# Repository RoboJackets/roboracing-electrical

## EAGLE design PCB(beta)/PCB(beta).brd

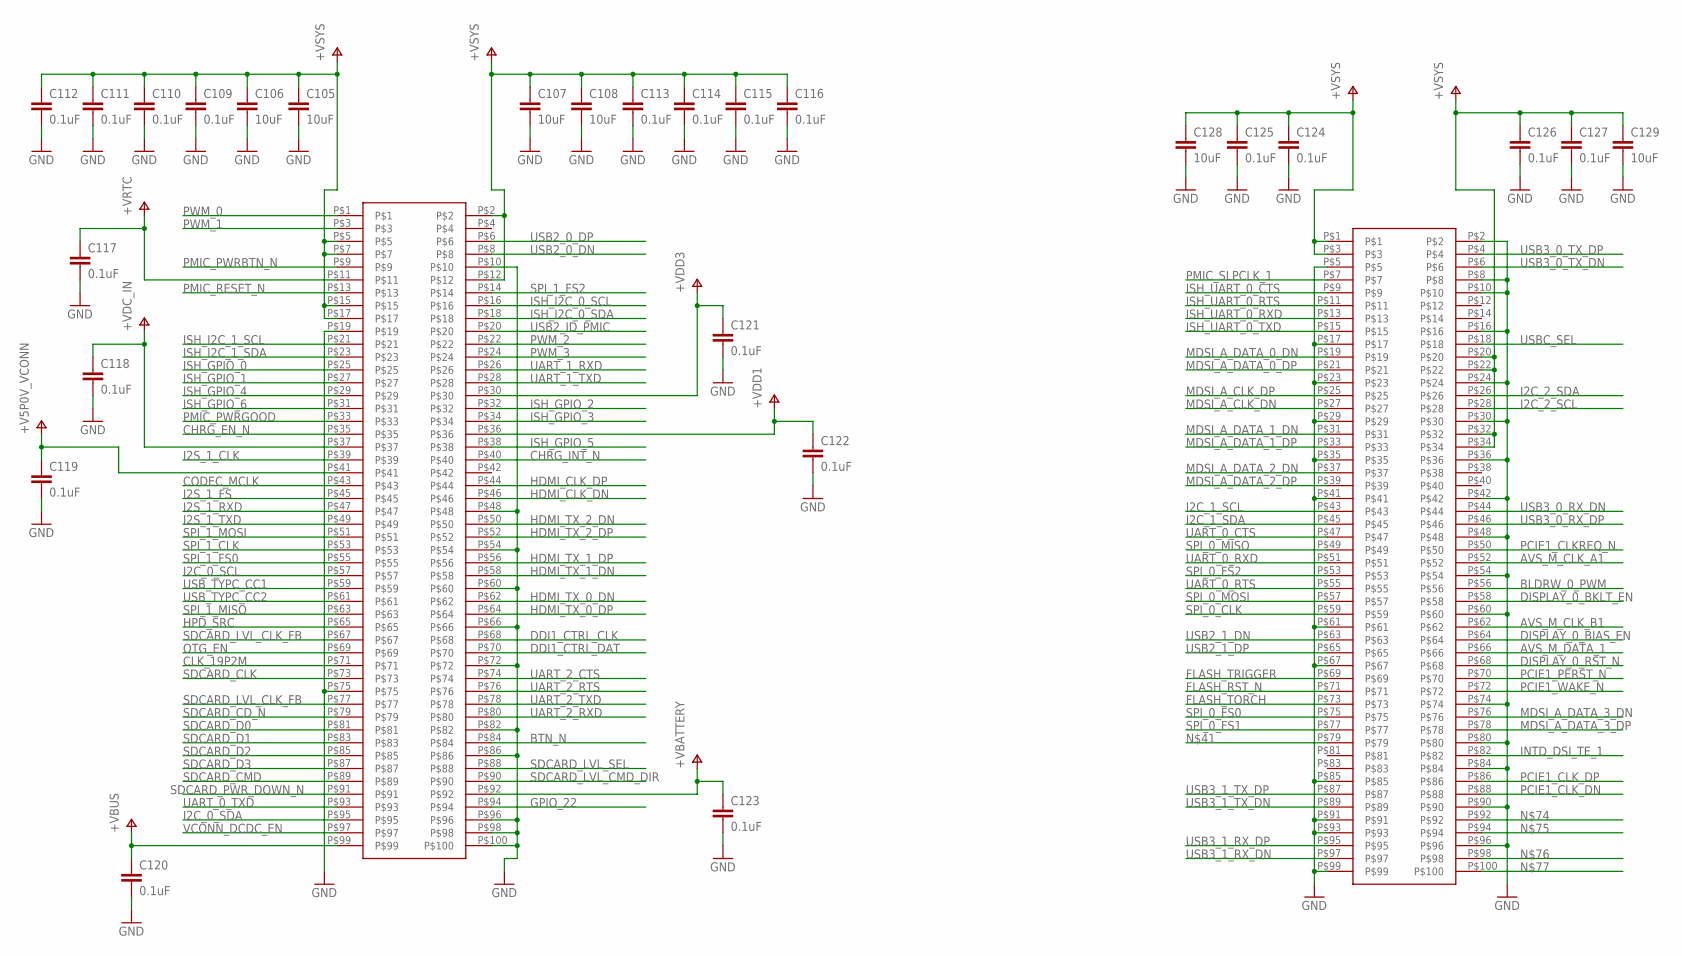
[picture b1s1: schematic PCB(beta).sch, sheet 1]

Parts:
C105, C106, C107, C108, C128, C129: 10uF; 0603
C109, C110, C111, C112, C113, C114, C115, C116, C117, C118, C119, C120, C121, C122, C123, C124, C125, C126, C127: 0.1uF; 0603
U$55, U$56: DF40C-100DS-0.4V(51)_100PINCONNECTOR; 100-DF40

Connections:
+V5P0V_VCONN: C119.1, U$55.P$41
+VBATTERY: C123.1, U$55.P$92; also elsewhere on the board
+VBUS: C120.1, U$55.P$99; also elsewhere on the board
+VDC_IN: C118.1, U$55.P$37; also elsewhere on the board
+VDD1: C122.1, U$55.P$36; also elsewhere on the board
+VDD3: C121.1, U$55.P$30; also elsewhere on the board
+VRTC: C117.1, U$55.P$11; also elsewhere on the board
+VSYS: C105.1, C106.1, C107.1, C108.1, C109.1, C110.1, C111.1, C112.1, C113.1, C114.1, C115.1, C116.1, U$55.P$2, U$55.P$5, U$55.P$7, U$55.P$12, U$55.P$15, U$55.P$17; also elsewhere on the board
AVS_M_CLK_A1: U$56.P$52; also elsewhere on the board
AVS_M_CLK_B1: U$56.P$62; also elsewhere on the board
AVS_M_DATA_1: U$56.P$66; also elsewhere on the board
BLDRW_0_PWM: U$56.P$56; also elsewhere on the board
BTN_N: U$55.P$84; also elsewhere on the board
CHRG_EN_N: U$55.P$35; also elsewhere on the board
CHRG_INT_N: U$55.P$40; also elsewhere on the board
CLK_19P2M: U$55.P$71; also elsewhere on the board
CODEC_MCLK: U$55.P$43; also elsewhere on the board
DDI1_CTRL_CLK: U$55.P$68; also elsewhere on the board
DDI1_CTRL_DAT: U$55.P$70; also elsewhere on the board
DISPLAY_0_BIAS_EN: U$56.P$64; also elsewhere on the board
DISPLAY_0_BKLT_EN: U$56.P$58; also elsewhere on the board
DISPLAY_0_RST_N: U$56.P$68; also elsewhere on the board
FLASH_RST_N: U$56.P$71; also elsewhere on the board
FLASH_TORCH: U$56.P$73; also elsewhere on the board
FLASH_TRIGGER: U$56.P$69; also elsewhere on the board
GND: C105.2, C106.2, C107.2, C108.2, C109.2, C110.2, C111.2, C112.2, C113.2, C114.2, C115.2, C116.2, C117.2, C118.2, C119.2, C120.2, C121.2, C122.2, C123.2, C124.2, C125.2, C126.2, C127.2, C128.2, C129.2, U$55.P$10, U$55.P$19, U$55.P$48, U$55.P$54, U$55.P$60, U$55.P$66, U$55.P$72, U$55.P$75, U$55.P$82, U$55.P$86, U$55.P$96, U$55.P$98, U$55.P$100, U$56.P$2, U$56.P$5, U$56.P$8, U$56.P$10, U$56.P$16, U$56.P$17, U$56.P$23, U$56.P$24, U$56.P$29, U$56.P$30, U$56.P$35, U$56.P$36, U$56.P$41, U$56.P$42, U$56.P$48, U$56.P$54, U$56.P$60, U$56.P$61, U$56.P$67, U$56.P$74, U$56.P$80, U$56.P$84, U$56.P$85, U$56.P$90, U$56.P$91, U$56.P$93, U$56.P$96, U$56.P$99; also elsewhere on the board
GPIO_22: U$55.P$94; also elsewhere on the board
HDMI_CLK_DN: U$55.P$46; also elsewhere on the board
HDMI_CLK_DP: U$55.P$44; also elsewhere on the board
HDMI_TX_0_DN: U$55.P$62; also elsewhere on the board
HDMI_TX_0_DP: U$55.P$64; also elsewhere on the board
HDMI_TX_1_DN: U$55.P$58; also elsewhere on the board
HDMI_TX_1_DP: U$55.P$56; also elsewhere on the board
HDMI_TX_2_DN: U$55.P$50; also elsewhere on the board
HDMI_TX_2_DP: U$55.P$52; also elsewhere on the board
HPD_SRC: U$55.P$65; also elsewhere on the board
I2C_0_SCL: U$55.P$57; also elsewhere on the board
I2C_0_SDA: U$55.P$95; also elsewhere on the board
I2C_1_SCL: U$56.P$43; also elsewhere on the board
I2C_1_SDA: U$56.P$45; also elsewhere on the board
I2C_2_SCL: U$56.P$28; also elsewhere on the board
I2C_2_SDA: U$56.P$26; also elsewhere on the board
I2S_1_CLK: U$55.P$39; also elsewhere on the board
I2S_1_FS: U$55.P$45; also elsewhere on the board
I2S_1_RXD: U$55.P$47; also elsewhere on the board
I2S_1_TXD: U$55.P$49; also elsewhere on the board
INTD_DSI_TE_1: U$56.P$82
ISH_GPIO_0: U$55.P$25; also elsewhere on the board
ISH_GPIO_1: U$55.P$27; also elsewhere on the board
ISH_GPIO_2: U$55.P$32; also elsewhere on the board
ISH_GPIO_3: U$55.P$34; also elsewhere on the board
ISH_GPIO_4: U$55.P$29; also elsewhere on the board
ISH_GPIO_5: U$55.P$38; also elsewhere on the board
ISH_GPIO_6: U$55.P$31; also elsewhere on the board
ISH_I2C_0_SCL: U$55.P$16; also elsewhere on the board
ISH_I2C_0_SDA: U$55.P$18; also elsewhere on the board
ISH_I2C_1_SCL: U$55.P$21; also elsewhere on the board
ISH_I2C_1_SDA: U$55.P$23; also elsewhere on the board
ISH_UART_0_CTS: U$56.P$9; also elsewhere on the board
ISH_UART_0_RTS: U$56.P$11; also elsewhere on the board
ISH_UART_0_RXD: U$56.P$13; also elsewhere on the board
ISH_UART_0_TXD: U$56.P$15; also elsewhere on the board
MDSI_A_CLK_DN: U$56.P$27
MDSI_A_CLK_DP: U$56.P$25
MDSI_A_DATA_0_DN: U$56.P$19
MDSI_A_DATA_0_DP: U$56.P$21
MDSI_A_DATA_1_DN: U$56.P$31
MDSI_A_DATA_1_DP: U$56.P$33
MDSI_A_DATA_2_DN: U$56.P$37
MDSI_A_DATA_2_DP: U$56.P$39
MDSI_A_DATA_3_DN: U$56.P$76
MDSI_A_DATA_3_DP: U$56.P$78
OTG_EN: U$55.P$69; also elsewhere on the board
PCIE1_CLKREQ_N: U$56.P$50
PCIE1_CLK_DN: U$56.P$88
PCIE1_CLK_DP: U$56.P$86
PCIE1_PERST_N: U$56.P$70
PCIE1_WAKE_N: U$56.P$72
PMIC_PWRBTN_N: U$55.P$9; also elsewhere on the board
PMIC_PWRGOOD: U$55.P$33; also elsewhere on the board
PMIC_RESET_N: U$55.P$13; also elsewhere on the board
PMIC_SLPCLK_1: U$56.P$7; also elsewhere on the board
PWM_0: U$55.P$1; also elsewhere on the board
PWM_1: U$55.P$3; also elsewhere on the board
PWM_2: U$55.P$22; also elsewhere on the board
PWM_3: U$55.P$24; also elsewhere on the board
SDCARD_CD_N: U$55.P$79; also elsewhere on the board
SDCARD_CLK: U$55.P$73; also elsewhere on the board
SDCARD_CMD: U$55.P$89; also elsewhere on the board
SDCARD_D0: U$55.P$81; also elsewhere on the board
SDCARD_D1: U$55.P$83; also elsewhere on the board
SDCARD_D2: U$55.P$85; also elsewhere on the board
SDCARD_D3: U$55.P$87; also elsewhere on the board
SDCARD_LVL_CLK_FB: U$55.P$67, U$55.P$77; also elsewhere on the board
SDCARD_LVL_CMD_DIR: U$55.P$90; also elsewhere on the board
SDCARD_LVL_SEL: U$55.P$88; also elsewhere on the board
SDCARD_PWR_DOWN_N: U$55.P$91; also elsewhere on the board
SPI_0_CLK: U$56.P$59; also elsewhere on the board
SPI_0_FS0: U$56.P$75; also elsewhere on the board
SPI_0_FS1: U$56.P$77; also elsewhere on the board
SPI_0_FS2: U$56.P$53; also elsewhere on the board
SPI_0_MISO: U$56.P$49; also elsewhere on the board
SPI_0_MOSI: U$56.P$57; also elsewhere on the board
SPI_1_CLK: U$55.P$53; also elsewhere on the board
SPI_1_FS0: U$55.P$55; also elsewhere on the board
SPI_1_FS2: U$55.P$14; also elsewhere on the board
SPI_1_MISO: U$55.P$63; also elsewhere on the board
SPI_1_MOSI: U$55.P$51; also elsewhere on the board
UART_0_CTS: U$56.P$47; also elsewhere on the board
UART_0_RTS: U$56.P$55; also elsewhere on the board
UART_0_RXD: U$56.P$51; also elsewhere on the board
UART_0_TXD: U$55.P$93; also elsewhere on the board
UART_1_RXD: U$55.P$26; also elsewhere on the board
UART_1_TXD: U$55.P$28; also elsewhere on the board
UART_2_CTS: U$55.P$74; also elsewhere on the board
UART_2_RTS: U$55.P$76; also elsewhere on the board
UART_2_RXD: U$55.P$80; also elsewhere on the board
UART_2_TXD: U$55.P$78; also elsewhere on the board
USB2_0_DN: U$55.P$8; also elsewhere on the board
USB2_0_DP: U$55.P$6; also elsewhere on the board
USB2_1_DN: U$56.P$63; also elsewhere on the board
USB2_1_DP: U$56.P$65; also elsewhere on the board
USB2_ID_PMIC: U$55.P$20
USB3_0_RX_DN: U$56.P$44; also elsewhere on the board
USB3_0_RX_DP: U$56.P$46; also elsewhere on the board
USB3_0_TX_DN: U$56.P$6; also elsewhere on the board
USB3_0_TX_DP: U$56.P$4; also elsewhere on the board
USB3_1_RX_DN: U$56.P$97; also elsewhere on the board
USB3_1_RX_DP: U$56.P$95; also elsewhere on the board
USB3_1_TX_DN: U$56.P$89; also elsewhere on the board
USB3_1_TX_DP: U$56.P$87; also elsewhere on the board
USBC_SEL: U$56.P$18; also elsewhere on the board
USB_TYPC_CC1: U$55.P$59; also elsewhere on the board
USB_TYPC_CC2: U$55.P$61; also elsewhere on the board
V+: C124.1, C125.1, C126.1, C127.1, C128.1, C129.1, U$56.P$1, U$56.P$3, U$56.P$20, U$56.P$22, U$56.P$32, U$56.P$34; also elsewhere on the board
VCONN_DCDC_EN: U$55.P$97; also elsewhere on the board

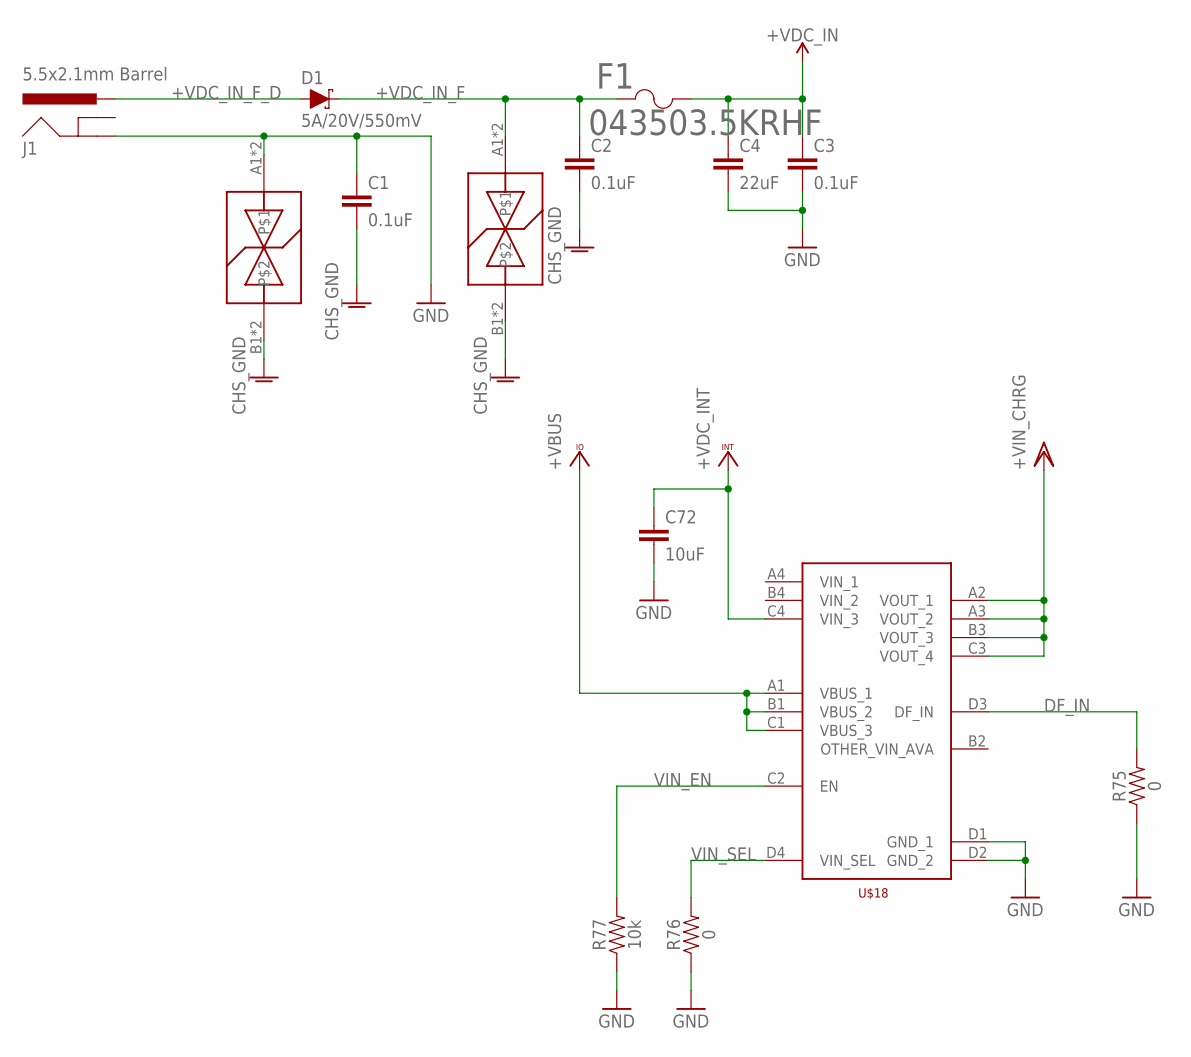
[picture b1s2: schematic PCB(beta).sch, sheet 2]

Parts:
C1, C2, C3: 0.1uF; 0603
C4: 22uF; 0805
C72: 10uF; 0603
D1: 5A/20V/550mV; SMA-DIODE
F1: 043503.5KRHF; 0435SERIES
J1: 5.5x2.1mm Barrel; POWER_JACK_SMD
R75, R76: 0; 0603
R77: 10k; 0603
U$2, U$3: LFTVS18-1F3_FLIPCHIP; 4-UFBGA
U$18: FPF3042UCX; 16-WLCSP

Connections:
+VBUS: U$18.A1 (VBUS_1), U$18.B1 (VBUS_2), U$18.C1 (VBUS_3); also elsewhere on the board
+VDC_IN: C3.1, C4.1, C72.1, F1.2, U$18.C4 (VIN_3); also elsewhere on the board
+VDC_IN_F: C2.1, D1.C, F1.1, U$2.A1, U$2.A2
+VDC_IN_F_D: D1.A, J1.VIN0 (PWR)
+VIN_CHRG: U$18.A2 (VOUT_1), U$18.A3 (VOUT_2), U$18.B3 (VOUT_3), U$18.C3 (VOUT_4); also elsewhere on the board
CHS_GND: C1.2, C2.2, U$2.B1, U$2.B2, U$3.B1, U$3.B2; also elsewhere on the board
DF_IN: R75.2, U$18.D3 (DF_IN)
GND: C1.1, C3.2, C4.2, C72.2, J1.P$4 (GND), R75.1, R76.1, R77.1, U$3.A1, U$3.A2, U$18.D1 (GND_1), U$18.D2 (GND_2); also elsewhere on the board
VIN_EN: R77.2, U$18.C2 (EN)
VIN_SEL: R76.2, U$18.D4 (VIN_SEL)

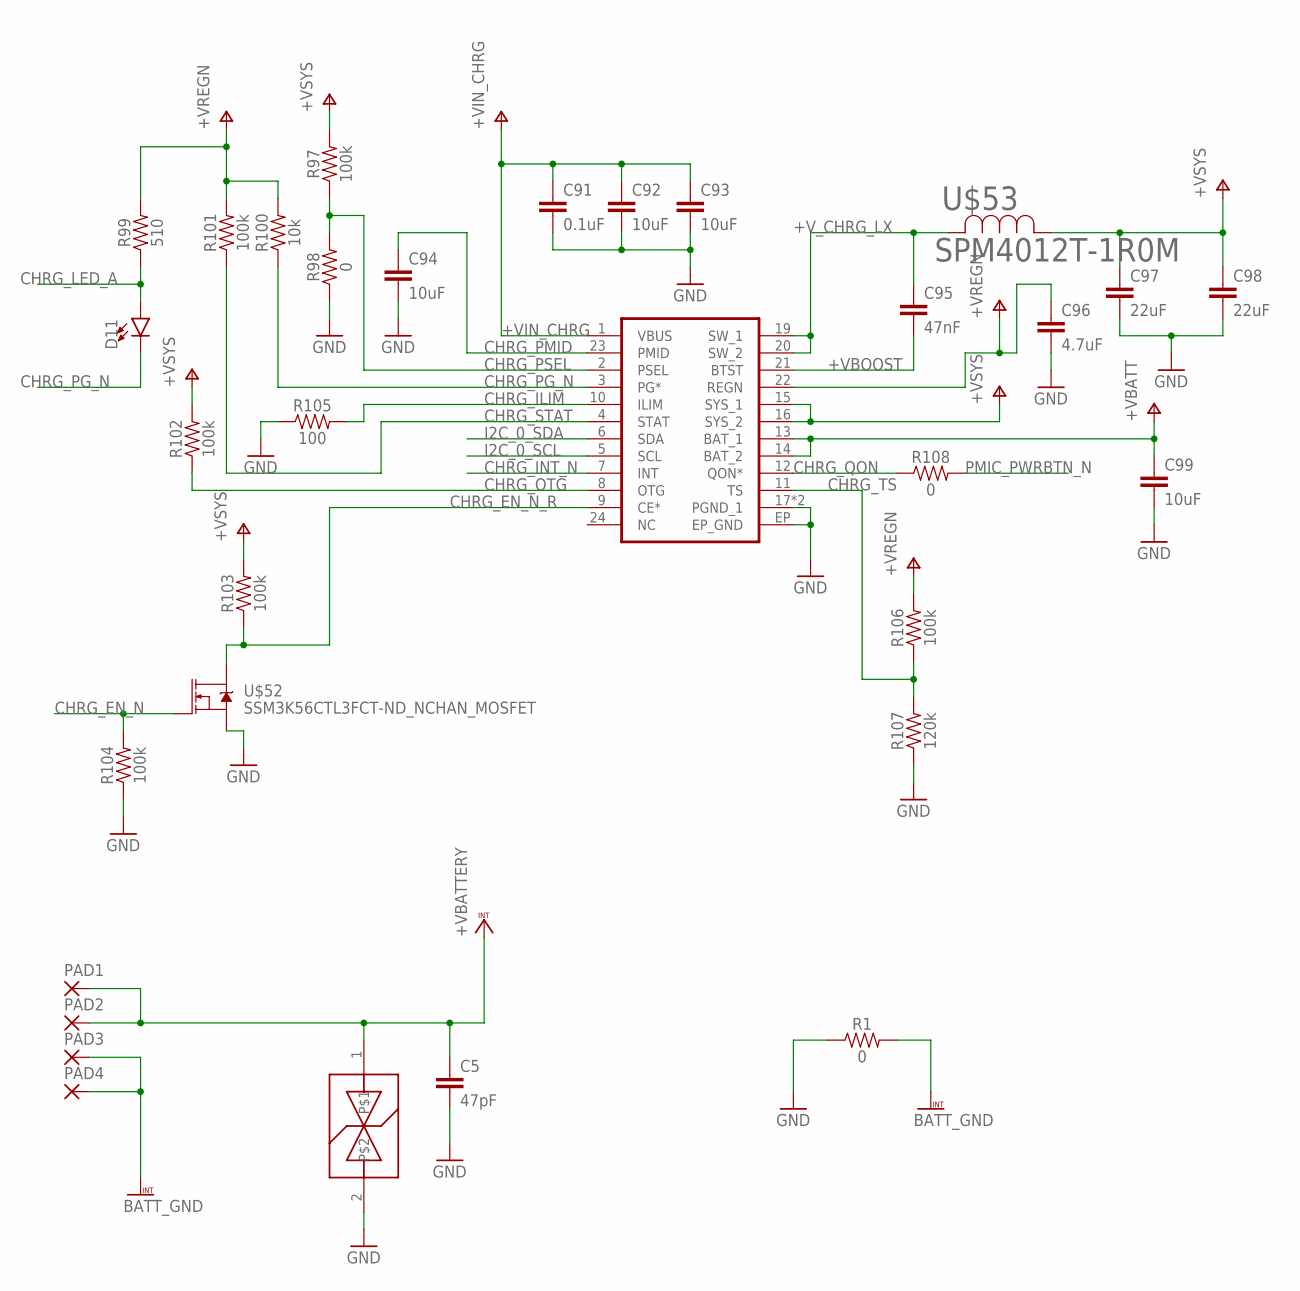
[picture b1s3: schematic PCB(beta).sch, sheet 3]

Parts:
C5: 47pF; 0603
C91: 0.1uF; 0603
C92, C93, C94, C99: 10uF; 0603
C95: 47nF; 0603
C96: 4.7uF; 0603
C97, C98: 22uF; 0805
D11: LED0603; LED-0603
PAD1, PAD2, PAD3, PAD4: 2,54/1,0
R1, R98, R108: 0; 0603
R97, R101, R102, R103, R104, R106: 100k; 0603
R99: 510; 2010
R100: 10k; 0603
R105: 100; 0603
R107: 120k; 0603
U$50: LXES15AAA1-100_ESD_SUPPRESSOR; 0402
U$51: BQ25892RTWT; WQFN-24
U$52: SSM3K56CTL3FCT-ND_NCHAN_MOSFET; 3-XFDFN
U$53: SPM4012T-1R0M; IND_SPM4020

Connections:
+VBATTERY: C5.1, PAD1.1, PAD2.1, U$50.1; also elsewhere on the board
+VBOOST: C95.2, U$51.21 (BTST)
+VIN_CHRG: C91.1, C92.1, C93.1, U$51.1 (VBUS); also elsewhere on the board
+VREGN: C96.1, R99.2, R100.2, R101.2, R106.2, U$51.22 (REGN)
+VSYS: C97.1, C98.1, R97.2, R102.2, R103.2, U$51.15 (SYS_1), U$51.16 (SYS_2), U$53.1; also elsewhere on the board
+V_CHRG_LX: C95.1, U$51.19 (SW_1), U$51.20 (SW_2), U$53.2
BATT_GND: PAD3.1, PAD4.1, R1.2
CHRG_EN_N: R104.2, U$52.P$1 (G); also elsewhere on the board
CHRG_EN_N_R: R103.1, U$51.9 (CE*), U$52.P$3 (D)
CHRG_ILIM: R105.2, U$51.10 (ILIM)
CHRG_INT_N: U$51.7 (INT); also elsewhere on the board
CHRG_LED_A: D11.A, R99.1
CHRG_OTG: R102.1, U$51.8 (OTG)
CHRG_PG_N: D11.C, R100.1, U$51.3 (PG*)
CHRG_PMID: C94.1, U$51.23 (PMID)
CHRG_PSEL: R97.1, R98.2, U$51.2 (PSEL)
CHRG_QON: R108.1, U$51.12 (QON*)
CHRG_STAT: R101.1, U$51.4 (STAT)
CHRG_TS: R106.1, R107.2, U$51.11 (TS)
GND: C5.2, C91.2, C92.2, C93.2, C94.2, C96.2, C97.2, C98.2, C99.2, R1.1, R98.1, R104.1, R105.1, R107.1, U$50.2, U$51.17 (PGND_1), U$51.18 (PGND_1), U$51.EP (EP_GND), U$52.P$2 (S); also elsewhere on the board
I2C_0_SCL: U$51.5 (SCL); also elsewhere on the board
I2C_0_SDA: U$51.6 (SDA); also elsewhere on the board
PMIC_PWRBTN_N: R108.2; also elsewhere on the board
V+: C99.1, U$51.13 (BAT_1), U$51.14 (BAT_2); also elsewhere on the board

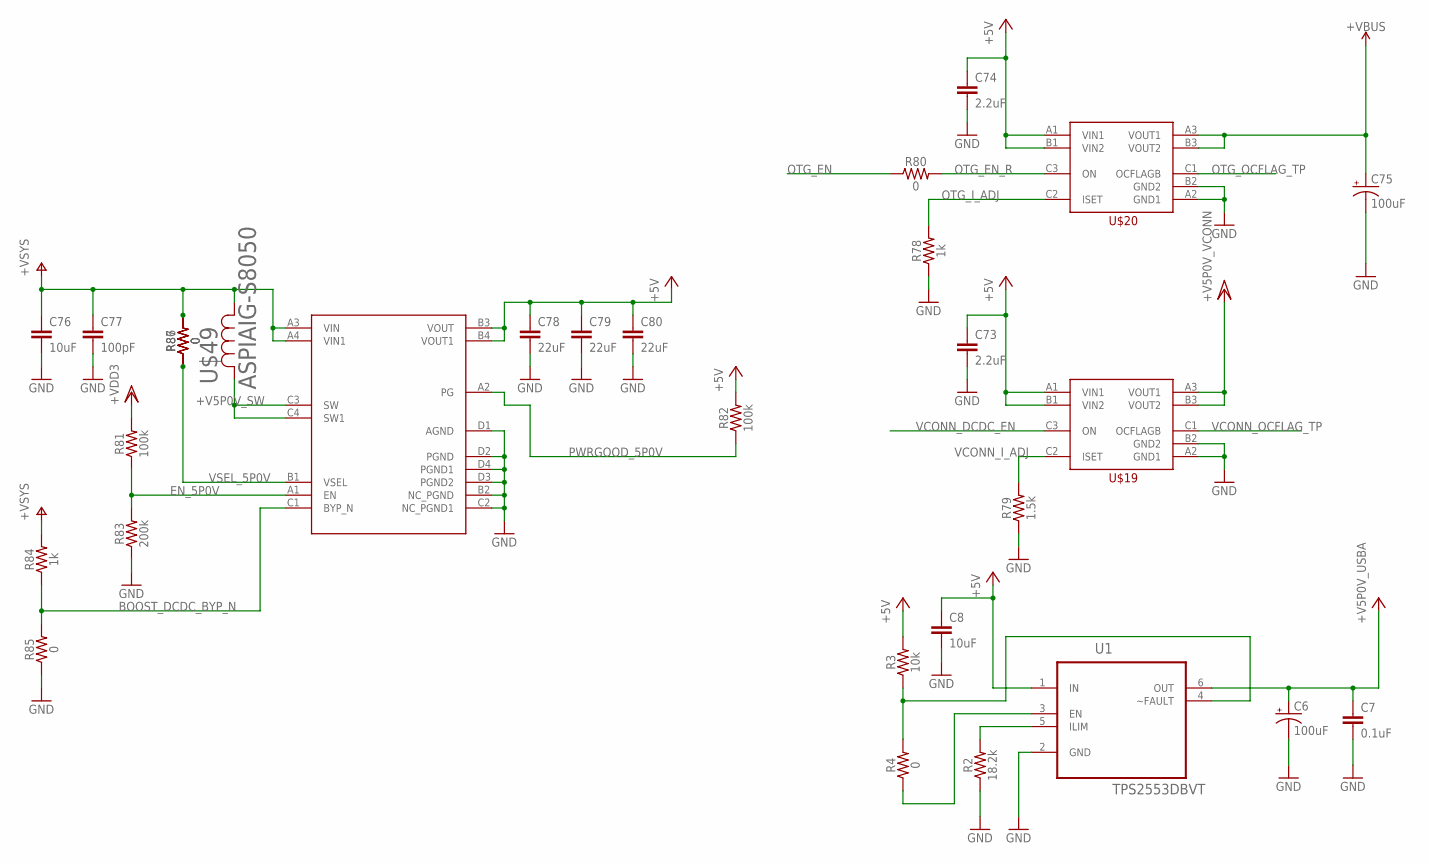
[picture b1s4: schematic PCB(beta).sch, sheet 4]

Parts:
C6: 100uF; EIA7343
C7: 0.1uF; 0603
C8, C76: 10uF; 0603
C73, C74: 2.2uF; 0603
C75: 100uF; NIC_10X10.5_CAP
C77: 100pF; 0603
C78, C79, C80: 22uF; 0805
R2: 18.2k; 0603
R3: 10k; 0603
R4, R80, R85, R86, R87: 0; 0603
R78, R84: 1k; 0603
R79: 1.5k; 0603
R81, R82: 100k; 0603
R83: 200k; 0603
U1: TPS2553DBVT; SOT95P280X145-6N
U$19, U$20: FPF2495UCX; 9-WLCSP
U$21: FAN48623UC50X_SWITCHING_REGULATOR; 16-WLCSP
U$49: ASPIAIG-S8050

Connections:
+5V: C8.1, C73.1, C74.1, C78.1, C79.1, C80.1, R3.2, R82.2, U1.1 (IN), U$19.A1 (VIN1), U$19.B1 (VIN2), U$20.A1 (VIN1), U$20.B1 (VIN2), U$21.B3 (VOUT), U$21.B4 (VOUT1); also elsewhere on the board
+V5P0V_CONN: U$19.A3 (VOUT1), U$19.B3 (VOUT2)
+V5P0V_SW: U$21.C3 (SW), U$21.C4 (SW1), U$49.2
+V5P0V_USBA: C6.A (+), C7.1, U1.6 (OUT)
+VBUS: C75.+, U$20.A3 (VOUT1), U$20.B3 (VOUT2); also elsewhere on the board
+VDD3: R81.2; also elsewhere on the board
+VSYS: C76.1, C77.1, R84.2, R86.2, R87.2, U$21.A3 (VIN), U$21.A4 (VIN1), U$49.1; also elsewhere on the board
BOOST_DCDC_BYP_N: R84.1, R85.2, U$21.C1 (BYP_N)
EN_5P0V: R81.1, R83.2, U$21.A1 (EN)
GND: C6.C (-), C7.2, C8.2, C73.2, C74.2, C75.-, C76.2, C77.2, C78.2, C79.2, C80.2, R2.1, R78.1, R79.1, R83.1, R85.1, U1.2 (GND), U$19.A2 (GND1), U$19.B2 (GND2), U$20.A2 (GND1), U$20.B2 (GND2), U$21.B2 (NC_PGND), U$21.C2 (NC_PGND1), U$21.D1 (AGND), U$21.D2 (PGND), U$21.D3 (PGND2), U$21.D4 (PGND1); also elsewhere on the board
unnamed: R2.2, U1.5 (ILIM)
OTG_EN: R80.1; also elsewhere on the board
OTG_EN_R: R80.2, U$20.C3 (ON)
OTG_I_ADJ: R78.2, U$20.C2 (ISET)
OTG_OCFLAG_TP: U$20.C1 (OCFLAGB)
PWRGOOD_5P0V: R82.1, U$21.A2 (PG)
USB3_CONN_EN: R4.1, U1.3 (EN)
USB3_CONN_FLT: R3.1, R4.2, U1.4 (~FAULT)
VCONN_DCDC_EN: U$19.C3 (ON); also elsewhere on the board
VCONN_I_ADJ: R79.2, U$19.C2 (ISET)
VCONN_OCFLAG_TP: U$19.C1 (OCFLAGB)
VSEL_5P0V: R86.1, R87.1, U$21.B1 (VSEL)

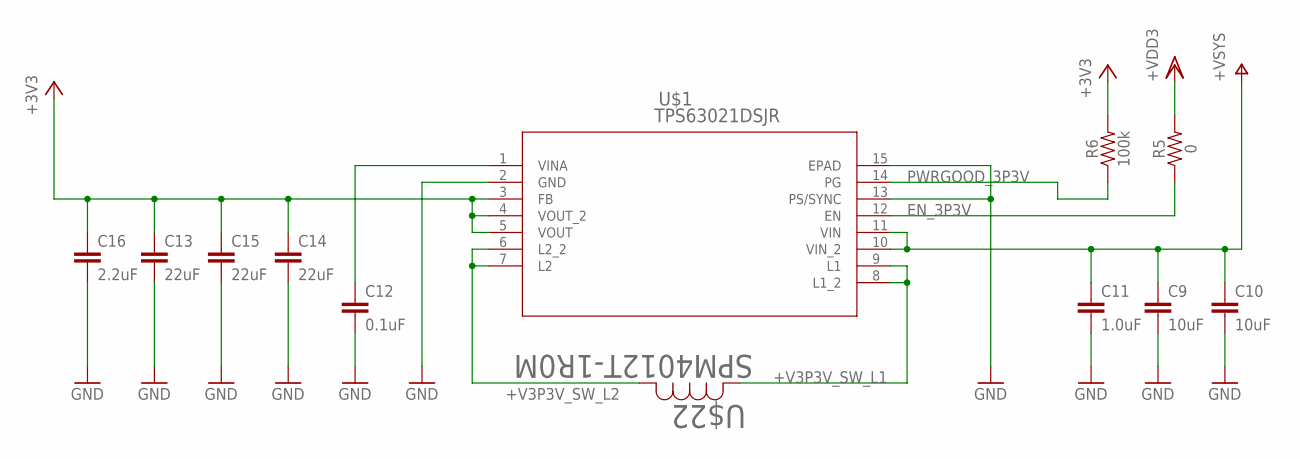
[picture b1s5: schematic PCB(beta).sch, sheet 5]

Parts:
C9, C10: 10uF; 0603
C11: 1.0uF; 0603
C12: 0.1uF; 0603
C13, C14, C15: 22uF; 0805
C16: 2.2uF; 0603
R5: 0; 0603
R6: 100k; 0603
U$1: TPS63021DSJR; DSJ14_2P85X1P58
U$22: SPM4012T-1R0M; IND_SPM4020

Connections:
+3V3: C13.1, C14.1, C15.1, C16.1, R6.2, U$1.3 (FB), U$1.4 (VOUT_2), U$1.5 (VOUT); also elsewhere on the board
+V3P3V_SW_L1: U$1.8 (L1_2), U$1.9 (L1), U$22.2
+V3P3V_SW_L2: U$1.6 (L2_2), U$1.7 (L2), U$22.1
+V3P3V_VINA: C12.1, U$1.1 (VINA)
+VDD3: R5.2; also elsewhere on the board
+VSYS: C9.1, C10.1, C11.1, U$1.10 (VIN_2), U$1.11 (VIN); also elsewhere on the board
EN_3P3V: R5.1, U$1.12 (EN)
GND: C9.2, C10.2, C11.2, C12.2, C13.2, C14.2, C15.2, C16.2, U$1.2 (GND), U$1.13 (PS/SYNC), U$1.15 (EPAD); also elsewhere on the board
PWRGOOD_3P3V: R6.1, U$1.14 (PG)

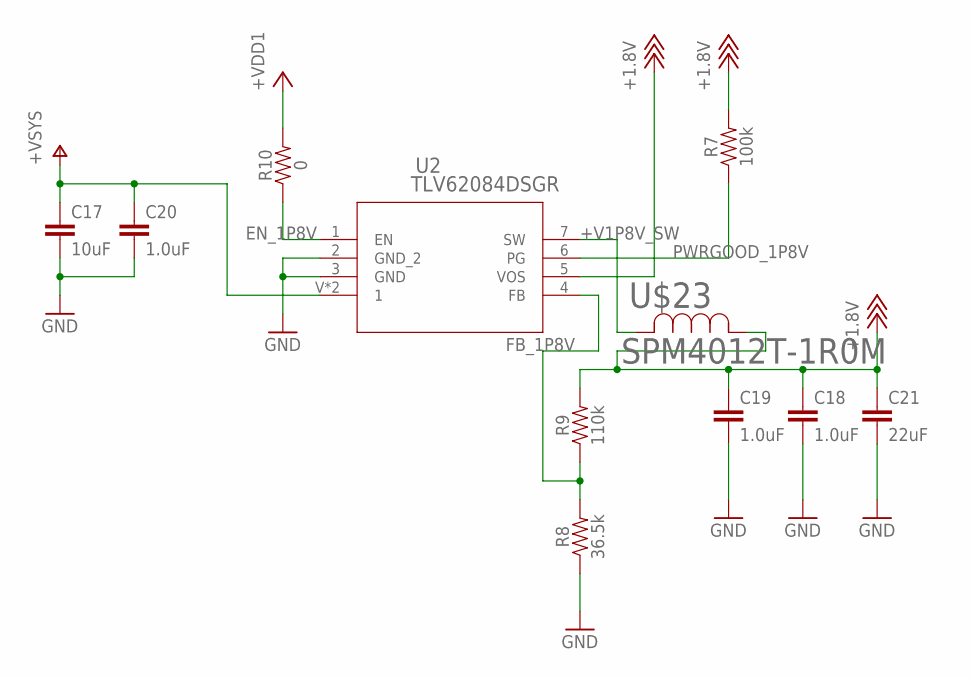
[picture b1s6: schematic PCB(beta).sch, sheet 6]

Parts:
C17: 10uF; 0603
C18, C19, C20: 1.0uF; 0603
C21: 22uF; 0805
R7: 100k; 0603
R8: 36.5k; 0603
R9: 110k; 0603
R10: 0; 0603
U2: TLV62084DSGR; DSG8_0P9X1P6
U$23: SPM4012T-1R0M; IND_SPM4020

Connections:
+1.8V: C18.1, C19.1, C21.1, R7.2, R9.2, U2.5 (VOS), U$23.1; also elsewhere on the board
+V1P8V_SW: U2.7 (SW), U$23.2
+VDD1: R10.2; also elsewhere on the board
+VSYS: C17.1, C20.1, U2.V (1), U2.V_1 (1); also elsewhere on the board
EN_1P8V: R10.1, U2.1 (EN)
FB_1P8V: R8.2, R9.1, U2.4 (FB)
GND: C17.2, C18.2, C19.2, C20.2, C21.2, R8.1, U2.2 (GND_2), U2.3 (GND); also elsewhere on the board
PWRGOOD_1P8V: R7.1, U2.6 (PG)

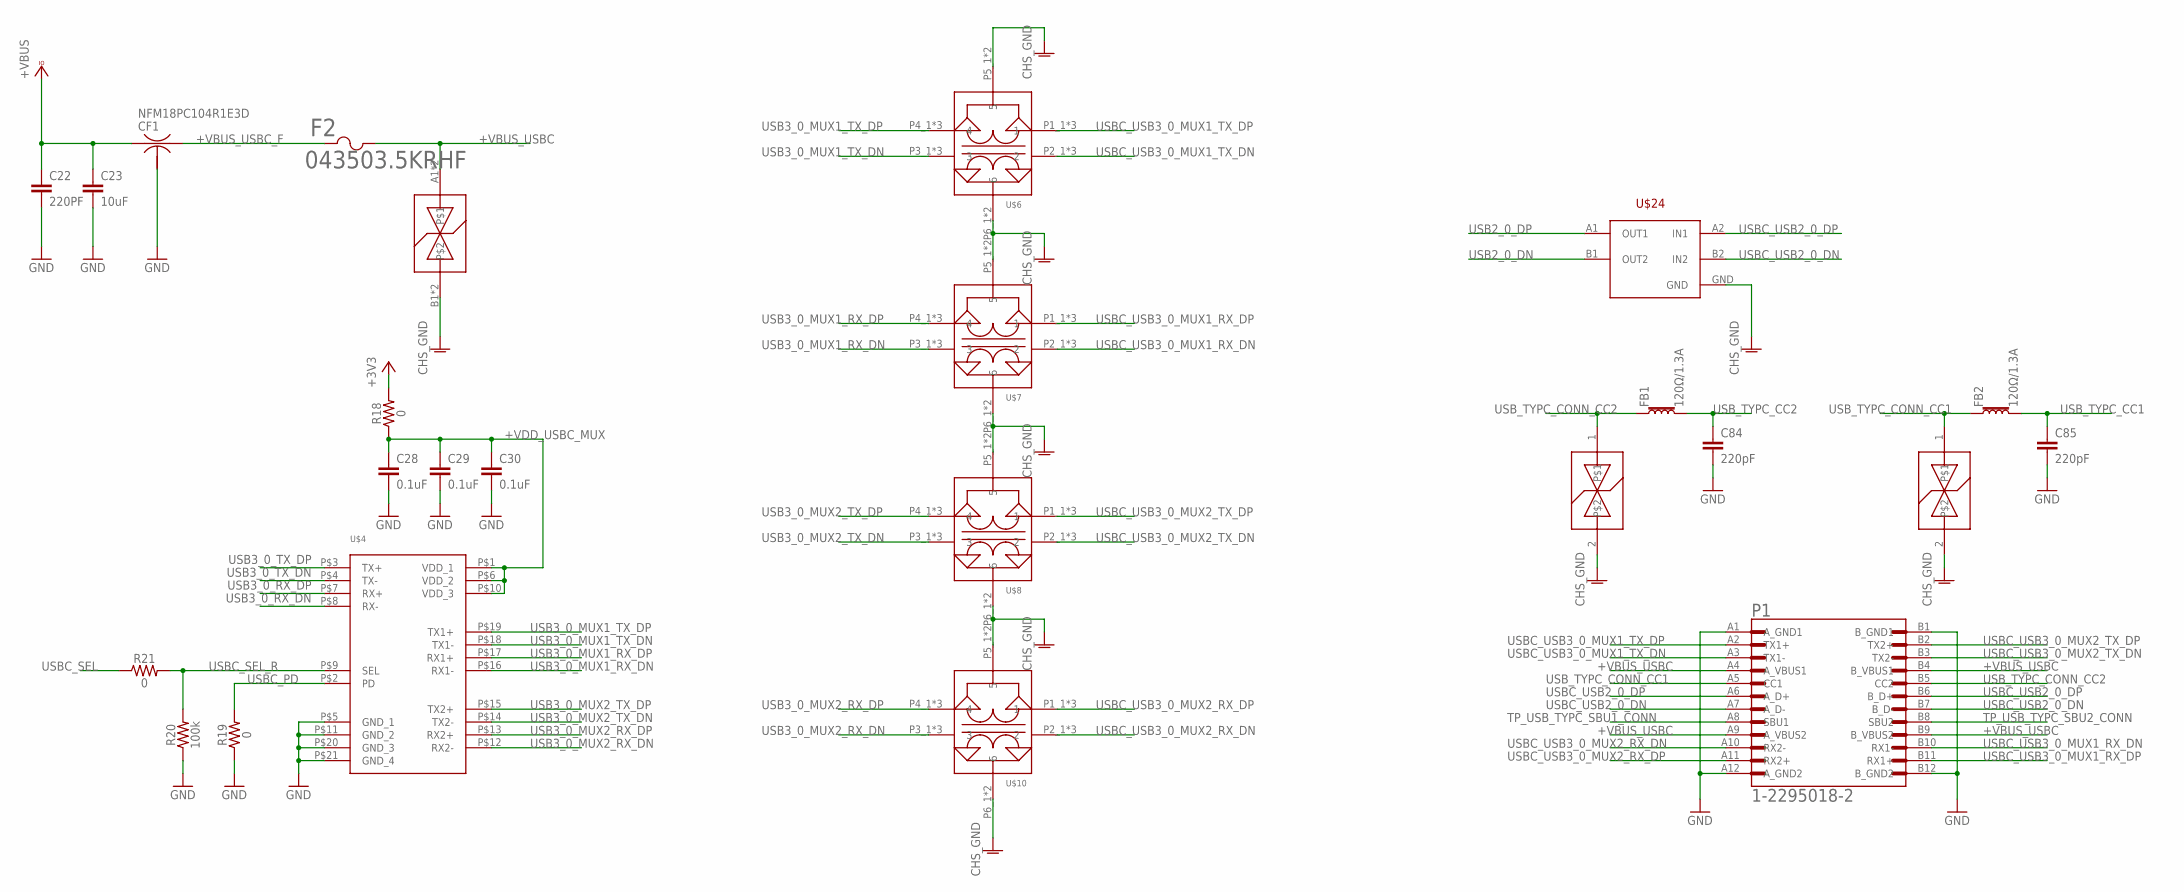
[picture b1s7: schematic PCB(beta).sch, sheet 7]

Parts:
C22: 220PF; 0603
C23: 10uF; 0603
C28, C29, C30: 0.1uF; 0603
C84, C85: 220pF; 0603
CF1: NFM18PC104R1E3D; NFM21C
F2: 043503.5KRHF; 0435SERIES
FB1, FB2: 120Ω/1.3A; 0603
P1: 1-2295018-2; TE_1-2295018-2
R18, R19, R21: 0; 0603
R20: 100k; 0603
U$4: PI3USB302-AZBEX_ANALOG_SWITCH; 20-TQFP
U$5: LFTVS18-1F3_FLIPCHIP; 4-UFBGA
U$6, U$7, U$8, U$10: TCE0806S-350-2P-T200; 0302_(0806_METRIC)
U$24: ECMF02-2BF3; 5-WLCSP
U$31, U$32: LXES15AAA1-100_ESD_SUPPRESSOR; 0402

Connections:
+3V3: R18.2; also elsewhere on the board
+VBUS: C22.1, C23.1, CF1.1; also elsewhere on the board
+VBUS_USBC: F2.2, P1.A4 (A_VBUS1), P1.A9 (A_VBUS2), P1.B4 (B_VBUS1), P1.B9 (B_VBUS2), U$5.A1, U$5.A2
+VBUS_USBC_F: CF1.3, F2.1
+VDD_USBC_MUX: C28.1, C29.1, C30.1, R18.1, U$4.P$1 (VDD_1), U$4.P$6 (VDD_2), U$4.P$10 (VDD_3)
CHS_GND: U$5.B1, U$5.B2, U$6.P5_1 (5), U$6.P5_2 (5), U$6.P6_1 (6), U$6.P6_2 (6), U$7.P5_1 (5), U$7.P5_2 (5), U$7.P6_1 (6), U$7.P6_2 (6), U$8.P5_1 (5), U$8.P5_2 (5), U$8.P6_1 (6), U$8.P6_2 (6), U$10.P5_1 (5), U$10.P5_2 (5), U$10.P6_1 (6), U$10.P6_2 (6), U$24.GND, U$31.2, U$32.2; also elsewhere on the board
GND: C22.2, C23.2, C28.2, C29.2, C30.2, C84.2, C85.2, CF1.2@1 (2), P1.A1 (A_GND1), P1.A12 (A_GND2), P1.B1 (B_GND1), P1.B12 (B_GND2), R19.1, R20.1, U$4.P$5 (GND_1), U$4.P$11 (GND_2), U$4.P$20 (GND_3), U$4.P$21 (GND_4); also elsewhere on the board
TP_USB_TYPC_SBU1_CONN: P1.A8 (SBU1)
TP_USB_TYPC_SBU2_CONN: P1.B8 (SBU2)
USB2_0_DN: U$24.B1 (OUT2); also elsewhere on the board
USB2_0_DP: U$24.A1 (OUT1); also elsewhere on the board
USB3_0_MUX1_RX_DN: U$4.P$16 (RX1-), U$7.P3_1 (3), U$7.P3_2 (3), U$7.P3_3 (3)
USB3_0_MUX1_RX_DP: U$4.P$17 (RX1+), U$7.P4_1 (4), U$7.P4_2 (4), U$7.P4_3 (4)
USB3_0_MUX1_TX_DN: U$4.P$18 (TX1-), U$6.P3_1 (3), U$6.P3_2 (3), U$6.P3_3 (3)
USB3_0_MUX1_TX_DP: U$4.P$19 (TX1+), U$6.P4_1 (4), U$6.P4_2 (4), U$6.P4_3 (4)
USB3_0_MUX2_RX_DN: U$4.P$12 (RX2-), U$10.P3_1 (3), U$10.P3_2 (3), U$10.P3_3 (3)
USB3_0_MUX2_RX_DP: U$4.P$13 (RX2+), U$10.P4_1 (4), U$10.P4_2 (4), U$10.P4_3 (4)
USB3_0_MUX2_TX_DN: U$4.P$14 (TX2-), U$8.P3_1 (3), U$8.P3_2 (3), U$8.P3_3 (3)
USB3_0_MUX2_TX_DP: U$4.P$15 (TX2+), U$8.P4_1 (4), U$8.P4_2 (4), U$8.P4_3 (4)
USB3_0_RX_DN: U$4.P$8 (RX-); also elsewhere on the board
USB3_0_RX_DP: U$4.P$7 (RX+); also elsewhere on the board
USB3_0_TX_DN: U$4.P$4 (TX-); also elsewhere on the board
USB3_0_TX_DP: U$4.P$3 (TX+); also elsewhere on the board
USBC_PD: R19.2, U$4.P$2 (PD)
USBC_SEL: R21.1; also elsewhere on the board
USBC_SEL_R: R20.2, R21.2, U$4.P$9 (SEL)
USBC_USB2_0_DN: P1.A7 (A_D-), P1.B7 (B_D-), U$24.B2 (IN2)
USBC_USB2_0_DP: P1.A6 (A_D+), P1.B6 (B_D+), U$24.A2 (IN1)
USBC_USB3_0_MUX1_RX_DN: P1.B10 (RX1-), U$7.P2_1 (2), U$7.P2_2 (2), U$7.P2_3 (2)
USBC_USB3_0_MUX1_RX_DP: P1.B11 (RX1+), U$7.P1_1 (1), U$7.P1_2 (1), U$7.P1_3 (1)
USBC_USB3_0_MUX1_TX_DN: P1.A3 (TX1-), U$6.P2_1 (2), U$6.P2_2 (2), U$6.P2_3 (2)
USBC_USB3_0_MUX1_TX_DP: P1.A2 (TX1+), U$6.P1_1 (1), U$6.P1_2 (1), U$6.P1_3 (1)
USBC_USB3_0_MUX2_RX_DN: P1.A10 (RX2-), U$10.P2_1 (2), U$10.P2_2 (2), U$10.P2_3 (2)
USBC_USB3_0_MUX2_RX_DP: P1.A11 (RX2+), U$10.P1_1 (1), U$10.P1_2 (1), U$10.P1_3 (1)
USBC_USB3_0_MUX2_TX_DN: P1.B3 (TX2-), U$8.P2_1 (2), U$8.P2_2 (2), U$8.P2_3 (2)
USBC_USB3_0_MUX2_TX_DP: P1.B2 (TX2+), U$8.P1_1 (1), U$8.P1_2 (1), U$8.P1_3 (1)
USB_TYPC_CC1: C85.1, FB2.2; also elsewhere on the board
USB_TYPC_CC2: C84.1, FB1.2; also elsewhere on the board
USB_TYPC_CONN_CC1: FB2.1, P1.A5 (CC1), U$32.1
USB_TYPC_CONN_CC2: FB1.1, P1.B5 (CC2), U$31.1

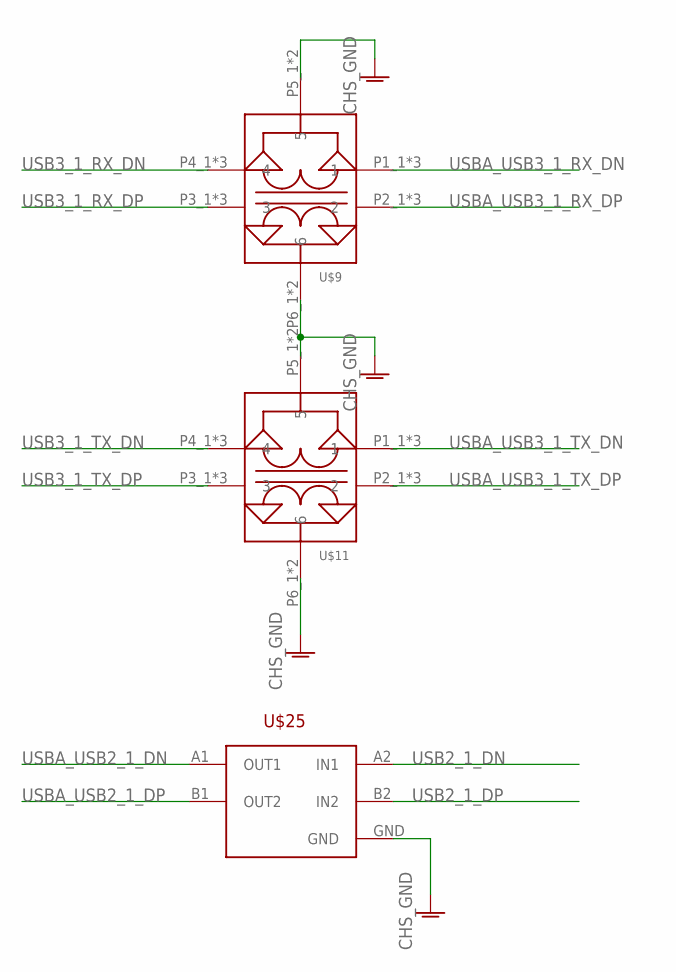
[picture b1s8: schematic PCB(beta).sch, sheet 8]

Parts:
U$9, U$11: TCE0806S-350-2P-T200; 0302_(0806_METRIC)
U$25: ECMF02-2BF3; 5-WLCSP

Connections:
CHS_GND: U$9.P5_1 (5), U$9.P5_2 (5), U$9.P6_1 (6), U$9.P6_2 (6), U$11.P5_1 (5), U$11.P5_2 (5), U$11.P6_1 (6), U$11.P6_2 (6), U$25.GND; also elsewhere on the board
USB2_1_DN: U$25.A2 (IN1); also elsewhere on the board
USB2_1_DP: U$25.B2 (IN2); also elsewhere on the board
USB3_1_RX_DN: U$9.P4_1 (4), U$9.P4_2 (4), U$9.P4_3 (4); also elsewhere on the board
USB3_1_RX_DP: U$9.P3_1 (3), U$9.P3_2 (3), U$9.P3_3 (3); also elsewhere on the board
USB3_1_TX_DN: U$11.P4_1 (4), U$11.P4_2 (4), U$11.P4_3 (4); also elsewhere on the board
USB3_1_TX_DP: U$11.P3_1 (3), U$11.P3_2 (3), U$11.P3_3 (3); also elsewhere on the board
USBA_USB2_1_DN: U$25.A1 (OUT1); also elsewhere on the board
USBA_USB2_1_DP: U$25.B1 (OUT2); also elsewhere on the board
USBA_USB3_1_RX_DN: U$9.P1_1 (1), U$9.P1_2 (1), U$9.P1_3 (1); also elsewhere on the board
USBA_USB3_1_RX_DP: U$9.P2_1 (2), U$9.P2_2 (2), U$9.P2_3 (2); also elsewhere on the board
USBA_USB3_1_TX_DN: U$11.P1_1 (1), U$11.P1_2 (1), U$11.P1_3 (1); also elsewhere on the board
USBA_USB3_1_TX_DP: U$11.P2_1 (2), U$11.P2_2 (2), U$11.P2_3 (2); also elsewhere on the board

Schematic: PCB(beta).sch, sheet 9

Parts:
C24, C25, C26, C27, C86: 0.1uF; 0603
D2, D3: 200mA/30V; SMA-DIODE
FB3: 120Ω/1.3A; 0603
IC1: FT232RQ; MLF32
J2: CONN_03; 1X03
J3: USB_MICRO-B_FEMALE-SMT; USB-B-MICRO-SMD
J4: FEMALE 2x3; 2X3
R11: 100k; 0603
R12, R13, R14, R15, R17: 10k; 0603
R16: 200k; 0603
U3: LSF0108RKSR; RKS20_1P1X3P1
U$26: ECMF02-2BF3; 5-WLCSP
U$33: LXES15AAA1-100_ESD_SUPPRESSOR; 0402

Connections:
+1.8V: C26.1, U3.2 (VREF_A); also elsewhere on the board
+3V3: R12.2, R13.2, R14.2, R15.2, R16.2; also elsewhere on the board
+5V: D3.A; also elsewhere on the board
+V3P3V_FT23RQ: C24.1, C25.1, IC1.1 (VCCIO), IC1.16 (3V3OUT)
+VFTDI_VCC_5P0V: D2.C, D3.C, IC1.19 (VCC)
+VUSB_IN: FB3.2, J3.VBUS, U$33.1
+VUSB_IN_FILT: C86.1, D2.A, FB3.1, R11.2
+VUSB_IN_FILT_R: J2.1, R11.1
CHS_GND: J3.SHIELD1 (SHIELD), J3.SHIELD2 (SHIELD), J3.SHIELD3 (SHIELD), U$26.GND, U$33.2; also elsewhere on the board
FTDI_USB_DN: IC1.15 (USBDM), U$26.A1 (OUT1)
FTDI_USB_DP: IC1.14 (USBDP), U$26.B1 (OUT2)
FTDI_USB_FILT_DN: J3.D-, U$26.A2 (IN1)
FTDI_USB_FILT_DP: J3.D+, U$26.B2 (IN2)
FTDI_USB_ID: J3.ID, R17.2
GND: C24.2, C25.2, C26.2, C27.2, C86.2, IC1.4 (GND1), IC1.17 (GND2), IC1.20 (GND3), IC1.24 (AGND), IC1.26 (TEST), J2.3, J3.GND, J4.1, R17.1, U3.1 (GND), U3.21 (EPAD); also elsewhere on the board
unnamed: C27.1, R16.1, U3.19 (VREF_B), U3.20 (EN)
RST_FT232RQ_N: IC1.18 (_RESET), J2.2
UART_2_CTS: U3.4 (A2); also elsewhere on the board
UART_2_CTS_LS: IC1.32 (_RTS), J4.6, R13.1, U3.17 (B2)
UART_2_RTS: U3.3 (A1); also elsewhere on the board
UART_2_RTS_LS: IC1.8 (_CTS), J4.2, R12.1, U3.18 (B1)
UART_2_RXD: U3.5 (A3); also elsewhere on the board
UART_2_RXD_LS: IC1.30 (TXD), J4.4, R14.1, U3.16 (B3)
UART_2_TXD: U3.6 (A4); also elsewhere on the board
UART_2_TXD_LS: IC1.2 (RXD), J4.5, R15.1, U3.15 (B4)

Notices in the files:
parts and their libraries:
SparkFun-Capacitors: Licensing: Creative Commons ShareAlike 4.0 International - https://creativecommons.org/licenses/by-sa/4.0
Wurth_Elektronik_Electromechanic_Input-O: Copyright: Würth Elektronik
